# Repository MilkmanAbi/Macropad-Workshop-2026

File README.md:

# SPIC Macropad Workshop 2026

<div align="center">

</div>

---

## “Yay! You made a custom keyboard… 😄”

“…Eh. A tiny one.”

**A MACROPAD!!! 😆✨**

SPIC Macropad Workshop 2026 💖

---

## What is this???

A macropad is a small programmable keyboard.

This one has **3 buttons**.

That sounds too small to matter…

…but it absolutely does.

You can turn it into:
- a productivity boost 😄  
- a media controller  
- a coding shortcut machine  
- or something completely unnecessary (but satisfying) 😆✨  

Basically: small device, big personality.

(￣ー￣)

---

## Why does this exist?

Because full keyboard firmware systems feel like too much pain for something this small.

So we don’t do that.

Instead:

- Plug it in  
- Edit a simple file  
- It works instantly  

No compiling. No waiting. No “why dis broken again” moments.

Just simple control. 💖

---

## What you’ll use

- CircuitPython  
- A RP2040 board  
- 3 buttons  
- 1 RGB LED that reflects your mode... or mood 😄✨  

That’s it.

And somehow, that’s enough.

(｡•̀ᴗ-)✧

---

## What it does

Each button can do different things depending on the mode.

For example:
- Copy / Paste / Cut  
- Volume control / media playback  
- Save / Undo / Redo  
- Zoom / Teams / Discord shortcuts  
- Or your own custom chaos 😆  

Same buttons. Different behaviour. New personality.

---

## Modes

The LED tells you what mode you are in.

And each mode changes what the 3 buttons do.

You’ll find:
- Clipboard mode 😄  
- Media mode  
- Coding mode 💖  
- Communication mode (Zoom / Teams / Discord)  
- Custom mode ✨  
- A “why did I do this” mode 😆  

(you’ll understand when you see it)

---

## Switching modes

Press Button 1 + Button 2 together.

The LED changes.

That’s it.

You are now in a different mode.

(￣▽￣)

---

## Custom mode

There is a simple config file where you can define your own setup.

You choose:
- what each button does  
- what color the LED shows  
- whether it behaves normally or becomes slightly unhinged (you'll see...) 😆✨  

No complicated setup. Just edit and save.

---

## Philosophy

This is not about building a complex system.

It’s about making something small feel useful and fun.

Fast to change. Easy to understand. Immediate feedback.

If it feels complicated, it is wrong. 💖

---

## SPIC Macropad Workshop 2026

You came in thinking:

“it’s just 3 buttons…”

You leave thinking:

“Small... But big in personality... Eh.” 😄✨

---

Credits to Organisers of 2025 Macropad Workshop and Jerick Seng

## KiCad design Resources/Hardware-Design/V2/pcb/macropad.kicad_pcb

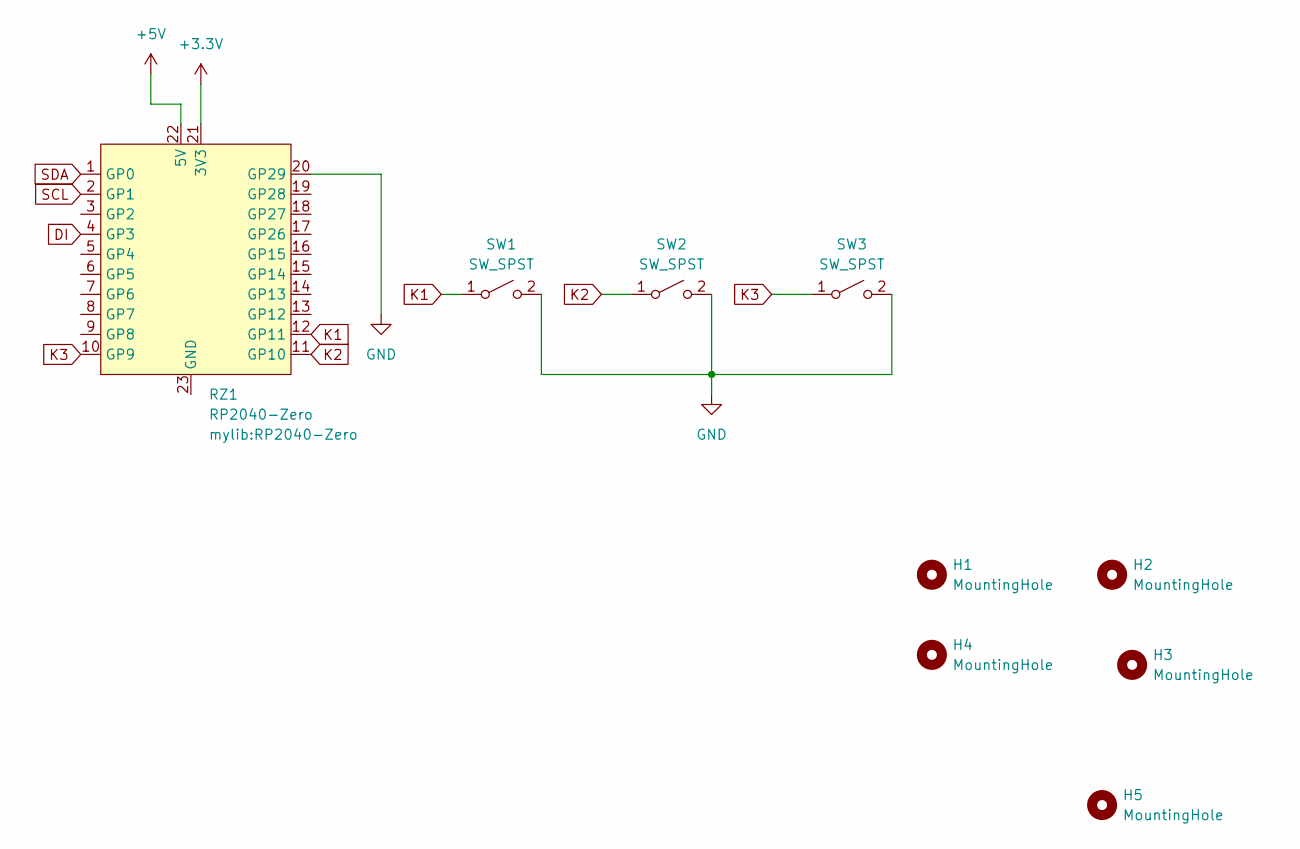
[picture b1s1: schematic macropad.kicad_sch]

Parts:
H1, H2, H3, H4, H5: MountingHole; MountingHole_5mm
RZ1: RP2040-Zero
SW1, SW2, SW3: SW_SPST; SW_Cherry_MX_1.00u_PCB

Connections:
+3.3V: RZ1.21 (3V3)
+5V: RZ1.22 (5V)
DI: RZ1.4 (GP3)
GND: RZ1.20 (GP29), SW1.2 (B), SW2.2 (B), SW3.2 (B)
K1: RZ1.12 (GP11), SW1.1 (A)
K2: RZ1.11 (GP10), SW2.1 (A)
K3: RZ1.10 (GP9), SW3.1 (A)
SCL: RZ1.2 (GP1)
SDA: RZ1.1 (GP0)

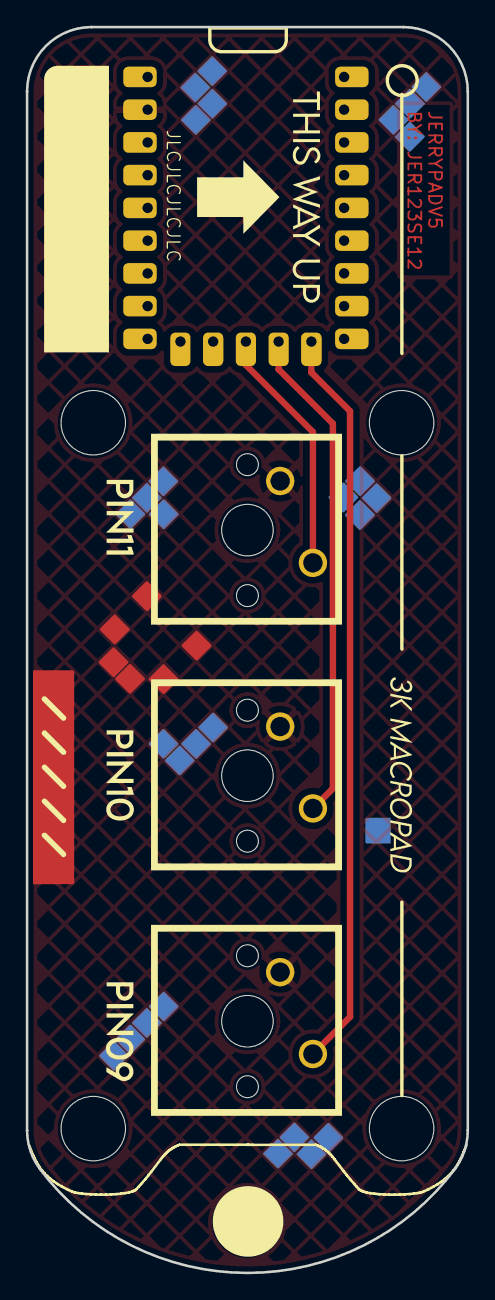
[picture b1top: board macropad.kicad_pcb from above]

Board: 2 copper layers, 34.2 x 96.7 mm, 9 parts (0 on the bottom side), 4 nets.

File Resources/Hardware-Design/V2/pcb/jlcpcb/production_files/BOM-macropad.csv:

Comment,Designator,Footprint,LCSC,Quantity
SW_SPST,SW1,SW_Cherry_MX_1.00u_PCB,,1
SW_SPST,SW2,SW_Cherry_MX_1.00u_PCB,,1
SW_SPST,SW3,SW_Cherry_MX_1.00u_PCB,,1
RP2040-Zero,RZ1,RP2040-Zero,,1

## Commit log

2026-04-11 SPIC Macropad Workshop 2026
2026-04-11 Add Resources folder
2026-04-11 Add credits for 2025 Macropad Workshop
2026-04-11 Meow Mrrow.
    Mrrp. Mrow? Miau Meowwwwwwwww. Mrp.
2026-04-16 Rename Layer 4 and update button actions
